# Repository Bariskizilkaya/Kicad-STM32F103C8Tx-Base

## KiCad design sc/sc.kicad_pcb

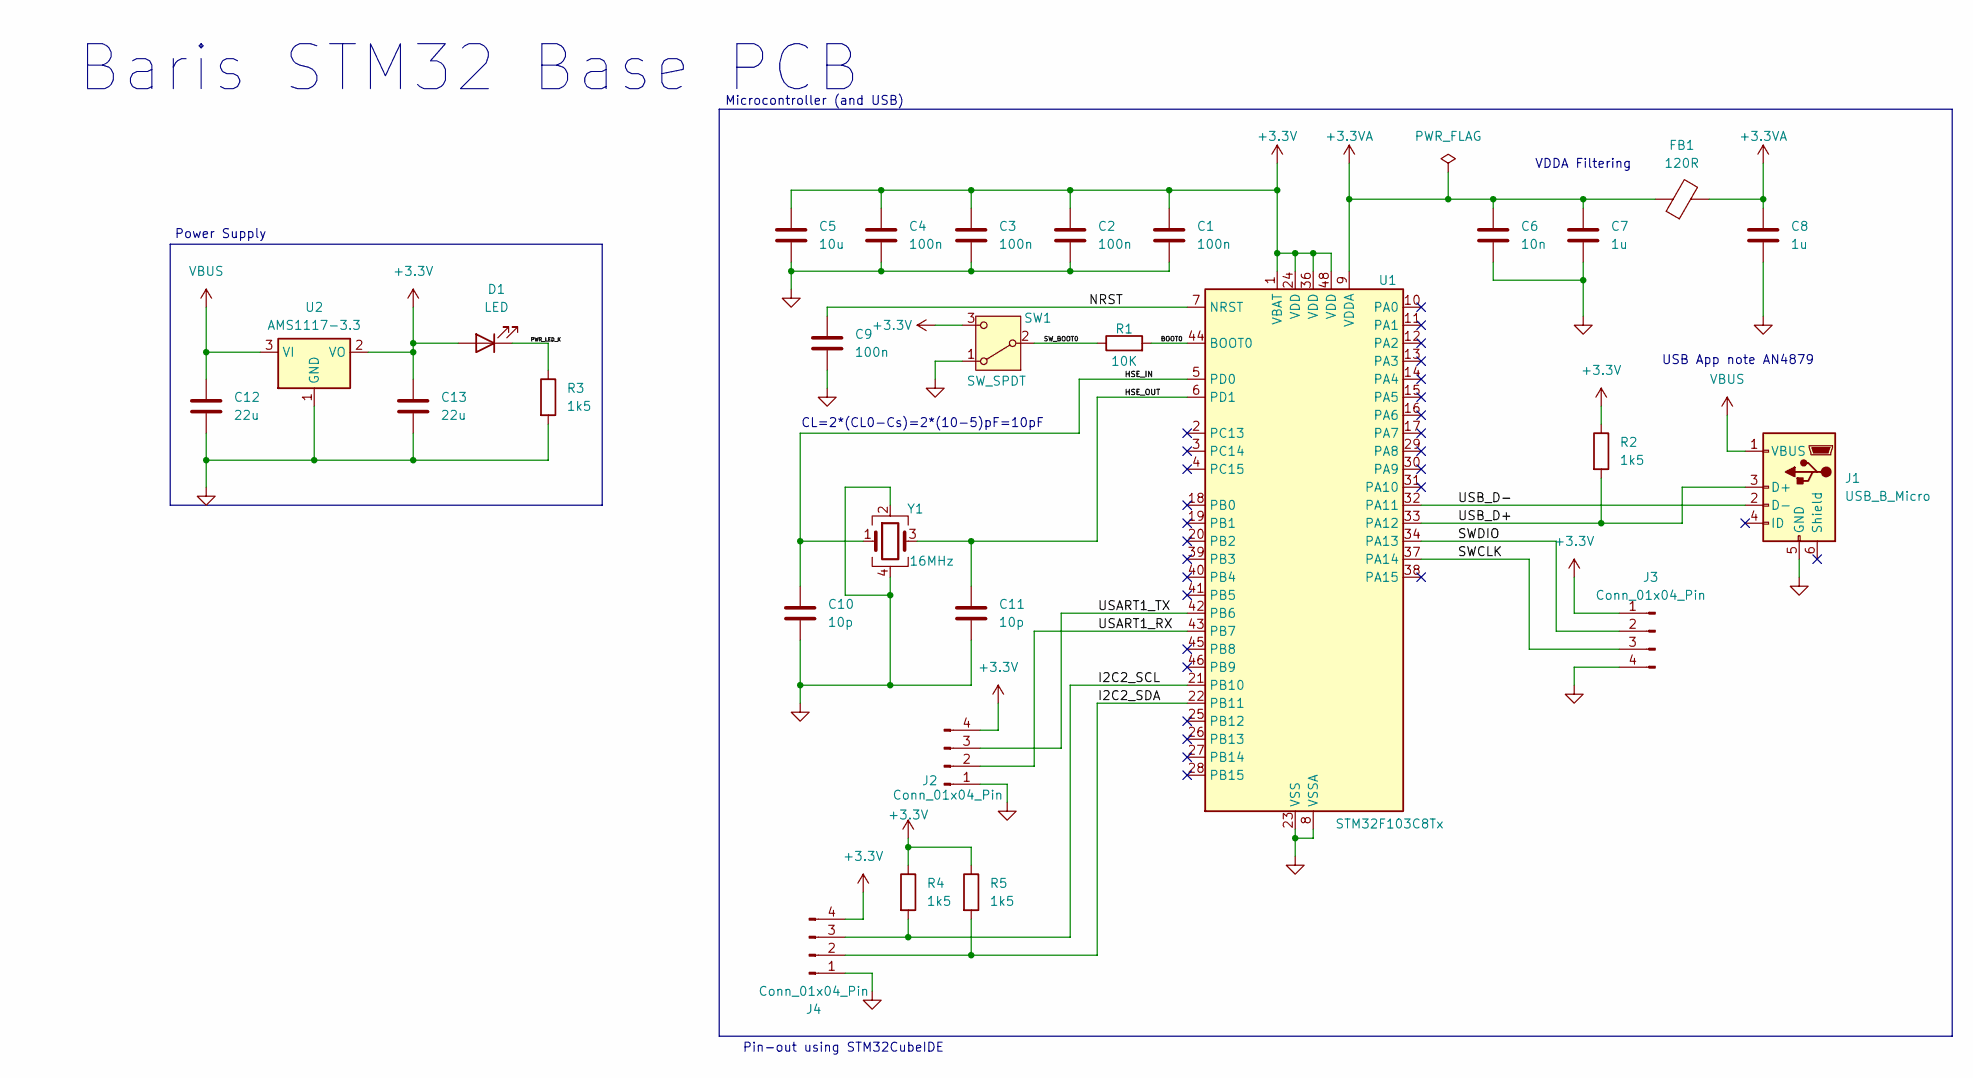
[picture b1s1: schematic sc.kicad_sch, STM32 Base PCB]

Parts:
C1, C2, C3, C4, C9: 100n; C_0402_1005Metric
C5: 10u; C_0603_1608Metric
C6: 10n; C_0402_1005Metric
C7, C8: 1u; C_0402_1005Metric
C10, C11: 10p; C_0402_1005Metric
C12, C13: 22u; C_0805_2012Metric
D1: LED; LED_0603_1608Metric
FB1: 120R; L_0603_1608Metric
J1: USB_B_Micro; USB_Micro-B_Wuerth_629105150521
J2, J3, J4: Conn_01x04_Pin; PinHeader_1x04_P2.54mm_Vertical
R1: 10K; R_0402_1005Metric
R2, R3, R4, R5: 1k5; R_0402_1005Metric
SW1: SW_SPDT; SW_SPDT_PCM12
U1: STM32F103C8Tx; LQFP-48_7x7mm_P0.5mm
U2: AMS1117-3.3; SOT-223-3_TabPin2
Y1: 16MHz; Crystal_SMD_3225-4Pin_3.2x2.5mm

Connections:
+3.3V: C1.1, C2.1, C3.1, C4.1, C5.1, C13.1, D1.2 (A), J2.4, J3.1, J4.4, R2.1, R4.1, R5.1, SW1.3 (C), U1.1 (VBAT), U1.24 (VDD), U1.36 (VDD), U1.48 (VDD), U2.2 (VO)
+3.3VA: C6.1, C7.1, C8.1, FB1.1, FB1.2, U1.9 (VDDA)
/BOOT0: R1.2, U1.44 (BOOT0)
/HSE_IN: C10.1, U1.5 (PD0), Y1.1
/HSE_OUT: C11.1, U1.6 (PD1), Y1.3
/I2C2_SCL: J4.3, R4.2, U1.21 (PB10)
/I2C2_SDA: J4.2, R5.2, U1.22 (PB11)
/NRST: C9.1, U1.7 (NRST)
/PWR_LED_K: D1.1 (K), R3.1
/SWCLK: J3.3, U1.37 (PA14)
/SWDIO: J3.2, U1.34 (PA13)
/SW_BOOT0: R1.1, SW1.2 (B)
/USART1_RX: J2.2, U1.43 (PB7)
/USART1_TX: J2.3, U1.42 (PB6)
/USB_D+: J1.3 (D+), R2.2, U1.33 (PA12)
/USB_D-: J1.2 (D-), U1.32 (PA11)
GND: C1.2, C2.2, C3.2, C4.2, C5.2, C6.2, C7.2, C8.2, C9.2, C10.2, C11.2, C12.2, C13.2, J1.5 (GND), J2.1, J3.4, J4.1, R3.2, SW1.1 (A), U1.8 (VSSA), U1.23 (VSS), U1.35 (VSS), U1.47 (VSS), U2.1 (GND), Y1.2, Y1.4
VBUS: C12.1, J1.1 (VBUS), U2.3 (VI)

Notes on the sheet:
Power Supply
Pin-out using STM32CubeIDE
VDDA Filtering
CL=2*(CL0-Cs)=2*(10-5)pF=10pF
Baris STM32 Base PCB
Microcontroller (and USB)
USB App note AN4879

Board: 2 copper layers, 28 parts (0 on the bottom side), 18 nets, no tracks yet.

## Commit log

2024-10-14 Kicad base for STM32F103
2024-10-14 Kicad base for STM32F103-2
2024-10-14 Updated scheme
2024-10-15 3D view has been added
